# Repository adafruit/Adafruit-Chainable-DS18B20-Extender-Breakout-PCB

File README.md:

## Adafruit Chainable DS18B20 Extender Breakout - STEMMA JST PH 2mm PCB

<a href="http://www.adafruit.com/products/5971"><br/>
Click here to purchase one from the Adafruit shop</a>

PCB files for the Adafruit Chainable DS18B20 Extender Breakout - STEMMA JST PH 2mm. 

Format is EagleCAD schematic and board layout
* https://www.adafruit.com/product/5971

### Description

One of the perks of working at adafruit is you get to request hardware - and you'll probably get fast turnaround! One of our adafruit.io developers requested "an easy way to chain DS18B20 sensors for testing with adafruit.io's wippersnapper service" at 11:54am one Monday morning, and after a few back-and-forth's we came up with the Adafruit Chainable DS18B20 Extender Breakout. Bit of a mouth-full, but we're better engineers than marketers doncha-know.

While there is absolutely nothing stopping you from just wiring up DS18B20's directly to your microcontroller, these extender breakouts will make things just a lil bit easier. You can use JST 3-pin cables to chain the extenders, the soldered-on screw terminal blocks mean you can easily connect DS18B20's in TO-92 or cable style with just a screwdriver. 

Each extender has a 4.7K signal pullup on board that can be disabled by cutting a trace, and a buffered signal LED that will let you know when there's data transmission on the 1-Wire line. When the red LED blinks, you know that data is going over the 1-wire line.

Please Note: This board doesn't come with a DS18B20 sensor itself; it's just an adapter-helper. You supply the sensor + a JST PH-compatible 3-pin cable.

### License

Adafruit invests time and resources providing this open source design, please support Adafruit and open-source hardware by purchasing products from [Adafruit](https://www.adafruit.com)!

Designed by Limor Fried/Ladyada for Adafruit Industries.

Creative Commons Attribution/Share-Alike, all text above must be included in any redistribution. 
See license.txt for additional details.

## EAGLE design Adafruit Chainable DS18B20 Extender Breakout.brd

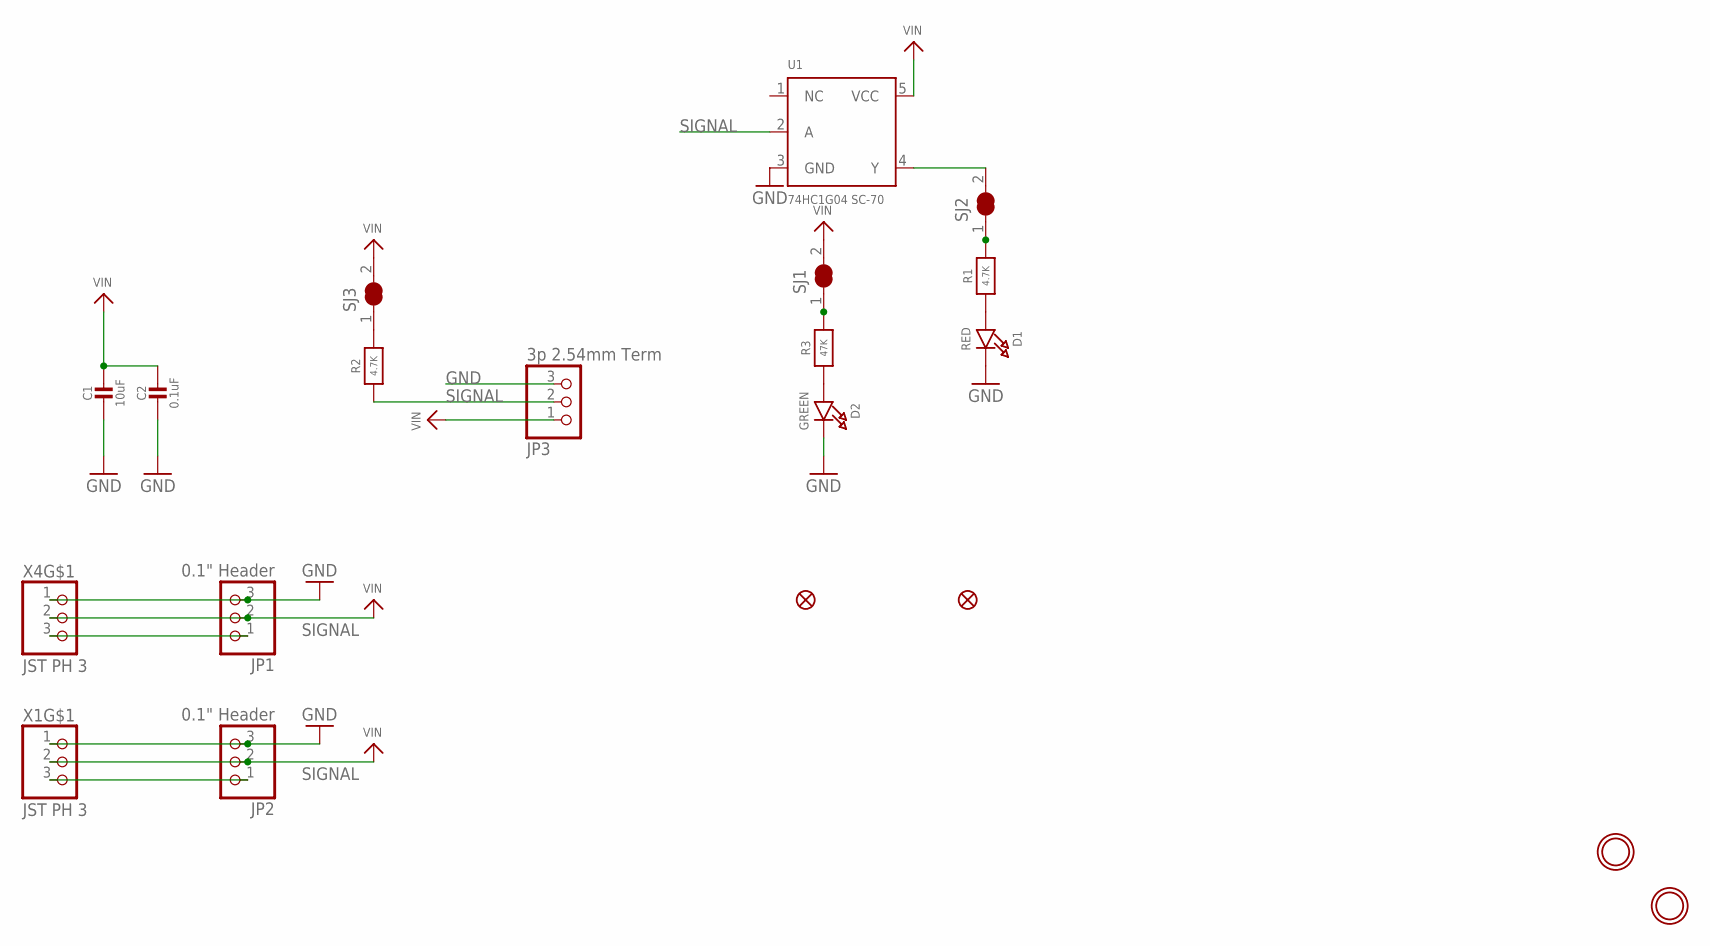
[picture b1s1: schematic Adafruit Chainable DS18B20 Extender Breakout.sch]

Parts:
C1: 10uF; 0805-NO
C2: 0.1uF; 0603-NO
D1: RED; CHIPLED_0603_NOOUTLINE
D2: GREEN; CHIPLED_0603_NOOUTLINE
FID2, FID3: FIDUCIAL_1MM
JP1, JP2: 0.1" Header; 1X03_OVAL
JP3: 3p 2.54mm Term; 1X03_2.54MMTERMINAL
R1, R2: 4.7K; 0603-NO
R3: 47K; 0603-NO
SJ1, SJ2, SJ3: SOLDERJUMPER_CLOSED; SOLDERJUMPER_CLOSEDWIRE
U1: 74HC1G04 SC-70; SC70-5
U$1, U$8: MOUNTINGHOLE2.0; MOUNTINGHOLE_2.0_PLATED
X1, X4: JST PH 3; JSTPH3

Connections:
GND: C1.2, C2.2, D1.C, D2.C, JP1.3, JP2.3, JP3.3, U1.3 (GND), X1.1, X4.1
unnamed: R3.2, SJ1.1
unnamed: D1.A, R1.1
unnamed: R1.2, SJ2.1
unnamed: R2.2, SJ3.1
unnamed: SJ2.2, U1.4 (Y)
unnamed: D2.A, R3.1
SIGNAL: JP1.1, JP2.1, JP3.2, R2.1, U1.2 (A), X1.3, X4.3
VIN: C1.1, C2.1, JP1.2, JP2.2, JP3.1, SJ1.2, SJ3.2, U1.5 (VCC), X1.2, X4.2

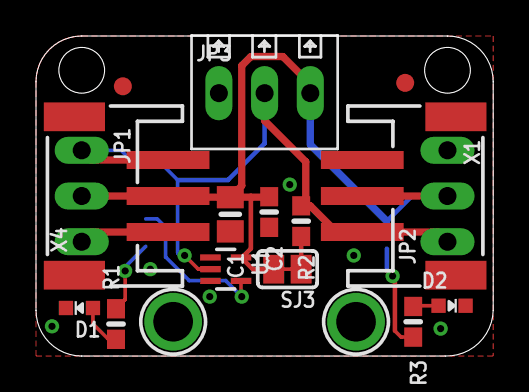
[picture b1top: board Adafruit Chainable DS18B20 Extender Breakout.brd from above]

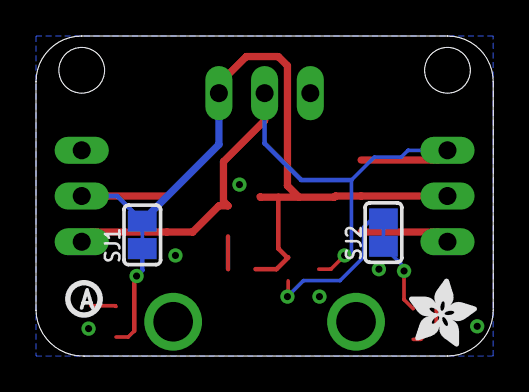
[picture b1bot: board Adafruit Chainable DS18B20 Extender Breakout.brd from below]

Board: 2 copper layers, 25.4 x 17.8 mm, 36 parts (11 on the bottom side), 9 nets.

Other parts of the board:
PLABEL0: PLABEL0
PLABEL1: PLABEL1
PLABEL13: PLABEL13
PLABEL14: PLABEL14
PLABEL15: PLABEL15
PLABEL16: PLABEL16
PLABEL17: PLABEL17
PLABEL18: PLABEL18
PLABEL19: PLABEL19
PLABEL20: PLABEL20
PLABEL21: PLABEL21
PLABEL22: PLABEL22
PLABEL24: PLABEL24
PLABEL25: PLABEL25
U$3: PCBFEAT-REV-040
U$12: ADAFRUIT_3.5MM

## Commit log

2024-06-03 cookiecutter

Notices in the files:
parts and their libraries:
microbuilder: This work is placed in the public domain, and may be freely used for commercial and non-commercial work with the following conditions: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
